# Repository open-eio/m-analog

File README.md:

Features:

- ADS1115 (16 bit 4 channel ADC)
- BMP180 (pressure and temp)
- SHT21 or SHT15 (temp and humidity)
- RFM69 radio

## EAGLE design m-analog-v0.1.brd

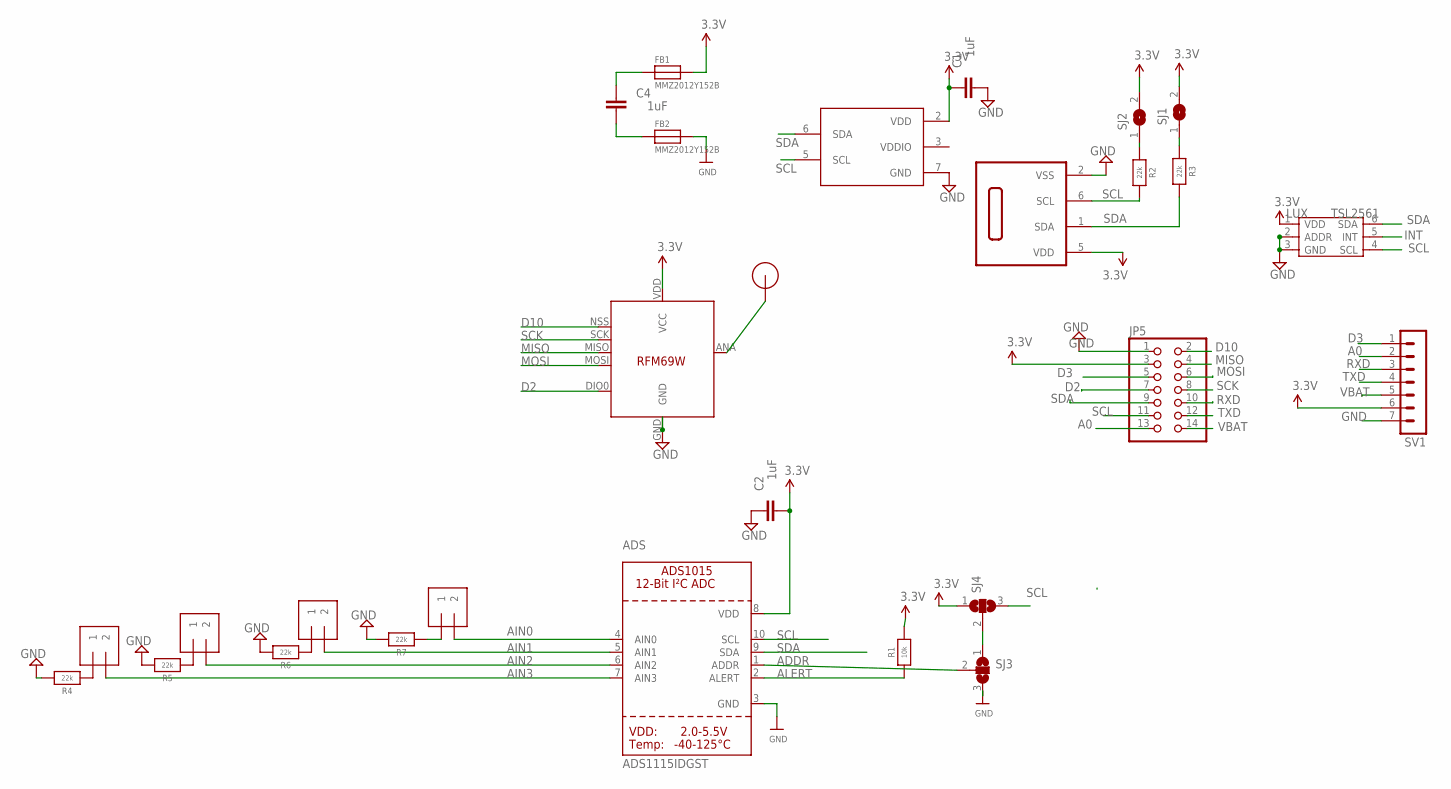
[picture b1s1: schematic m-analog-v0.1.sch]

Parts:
ADS: ADS1115IDGST; MSOP10
C1, C2, C4: 1uF; 0603-CAP
FB1, FB2: MMZ2012Y152B; 0805
IN0, IN1, IN2, IN3: 1X2-3.5MM
JP5: PINHD-2X7; 2X07
LUX: TSL2561; TMB-6
R1: 10k; 0603-NO
R2, R3, R4, R5, R6, R7: 22k; 0603-NO
SJ1, SJ2: SJ
SJ3, SJ4: SJ2W; SJ_2
SN1: SHT21; DFN6/SHT
SV1: MA07-1
U1: BMP180
U$1: RFM12B_ANTENNA; RFM12B-ANTENNA
U$5: RFM69; RFM69W-MINPADS

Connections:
A0: JP5.13, SV1.2
ADDR: ADS.1 (ADDR), SJ3.2
AIN0: ADS.4 (AIN0), IN0.2
AIN1: ADS.5 (AIN1), IN1.2
AIN2: ADS.6 (AIN2), IN2.2
AIN3: ADS.7 (AIN3), IN3.2
ALERT: ADS.2 (ALERT), R1.1
D2: JP5.7, U$5.DIO0
D3: JP5.5, SV1.1
D10: JP5.2, U$5.NSS (SEL)
GND: ADS.3 (GND), C1.1, C2.2, FB2.2, JP5.1, LUX.2 (ADDR), LUX.3 (GND), R4.2, R5.2, R6.2, R7.2, SJ3.3, SN1.2 (VSS), SV1.7, U1.7 (GND), U$5.GND
INT: LUX.5 (INT)
MISO: JP5.4, U$5.MISO
MOSI: JP5.6, U$5.MOSI
unnamed: C4.2, FB1.1
unnamed: C4.1, FB2.1
unnamed: SJ3.1, SJ4.2
unnamed: R3.1, SJ1.1
unnamed: R2.1, SJ2.1
unnamed: IN3.1, R4.1
unnamed: IN2.1, R5.1
unnamed: IN1.1, R6.1
unnamed: IN0.1, R7.1
unnamed: U$1.P$1, U$5.ANA (ANT)
RXD: JP5.10, SV1.3
SCK: JP5.8, U$5.SCK
SCL: ADS.10 (SCL), JP5.11, LUX.4 (SCL), R2.2, SJ4.3, SN1.6 (SCL), U1.5 (SCL)
SDA: ADS.9 (SDA), JP5.9, LUX.6 (SDA), R3.2, SN1.1 (SDA), U1.6 (SDA)
TXD: JP5.12, SV1.4
VBAT: JP5.14, SV1.5
VCC: ADS.8 (VDD), C1.2, C2.1, FB1.2, JP5.3, LUX.1 (VDD), R1.2, SJ1.2, SJ2.2, SJ4.1, SN1.5 (VDD), SV1.6, U1.2 (VDD), U$5.VDD (VCC)
VDDIO: U1.3 (VDDIO)

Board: 2 copper layers, 28 parts (4 on the bottom side), 30 nets, no tracks yet.

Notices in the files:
parts and their libraries:
microbuilder: This work is placed in the public domain, and may be freely used for commercial and non-commercial work with the following conditions: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
